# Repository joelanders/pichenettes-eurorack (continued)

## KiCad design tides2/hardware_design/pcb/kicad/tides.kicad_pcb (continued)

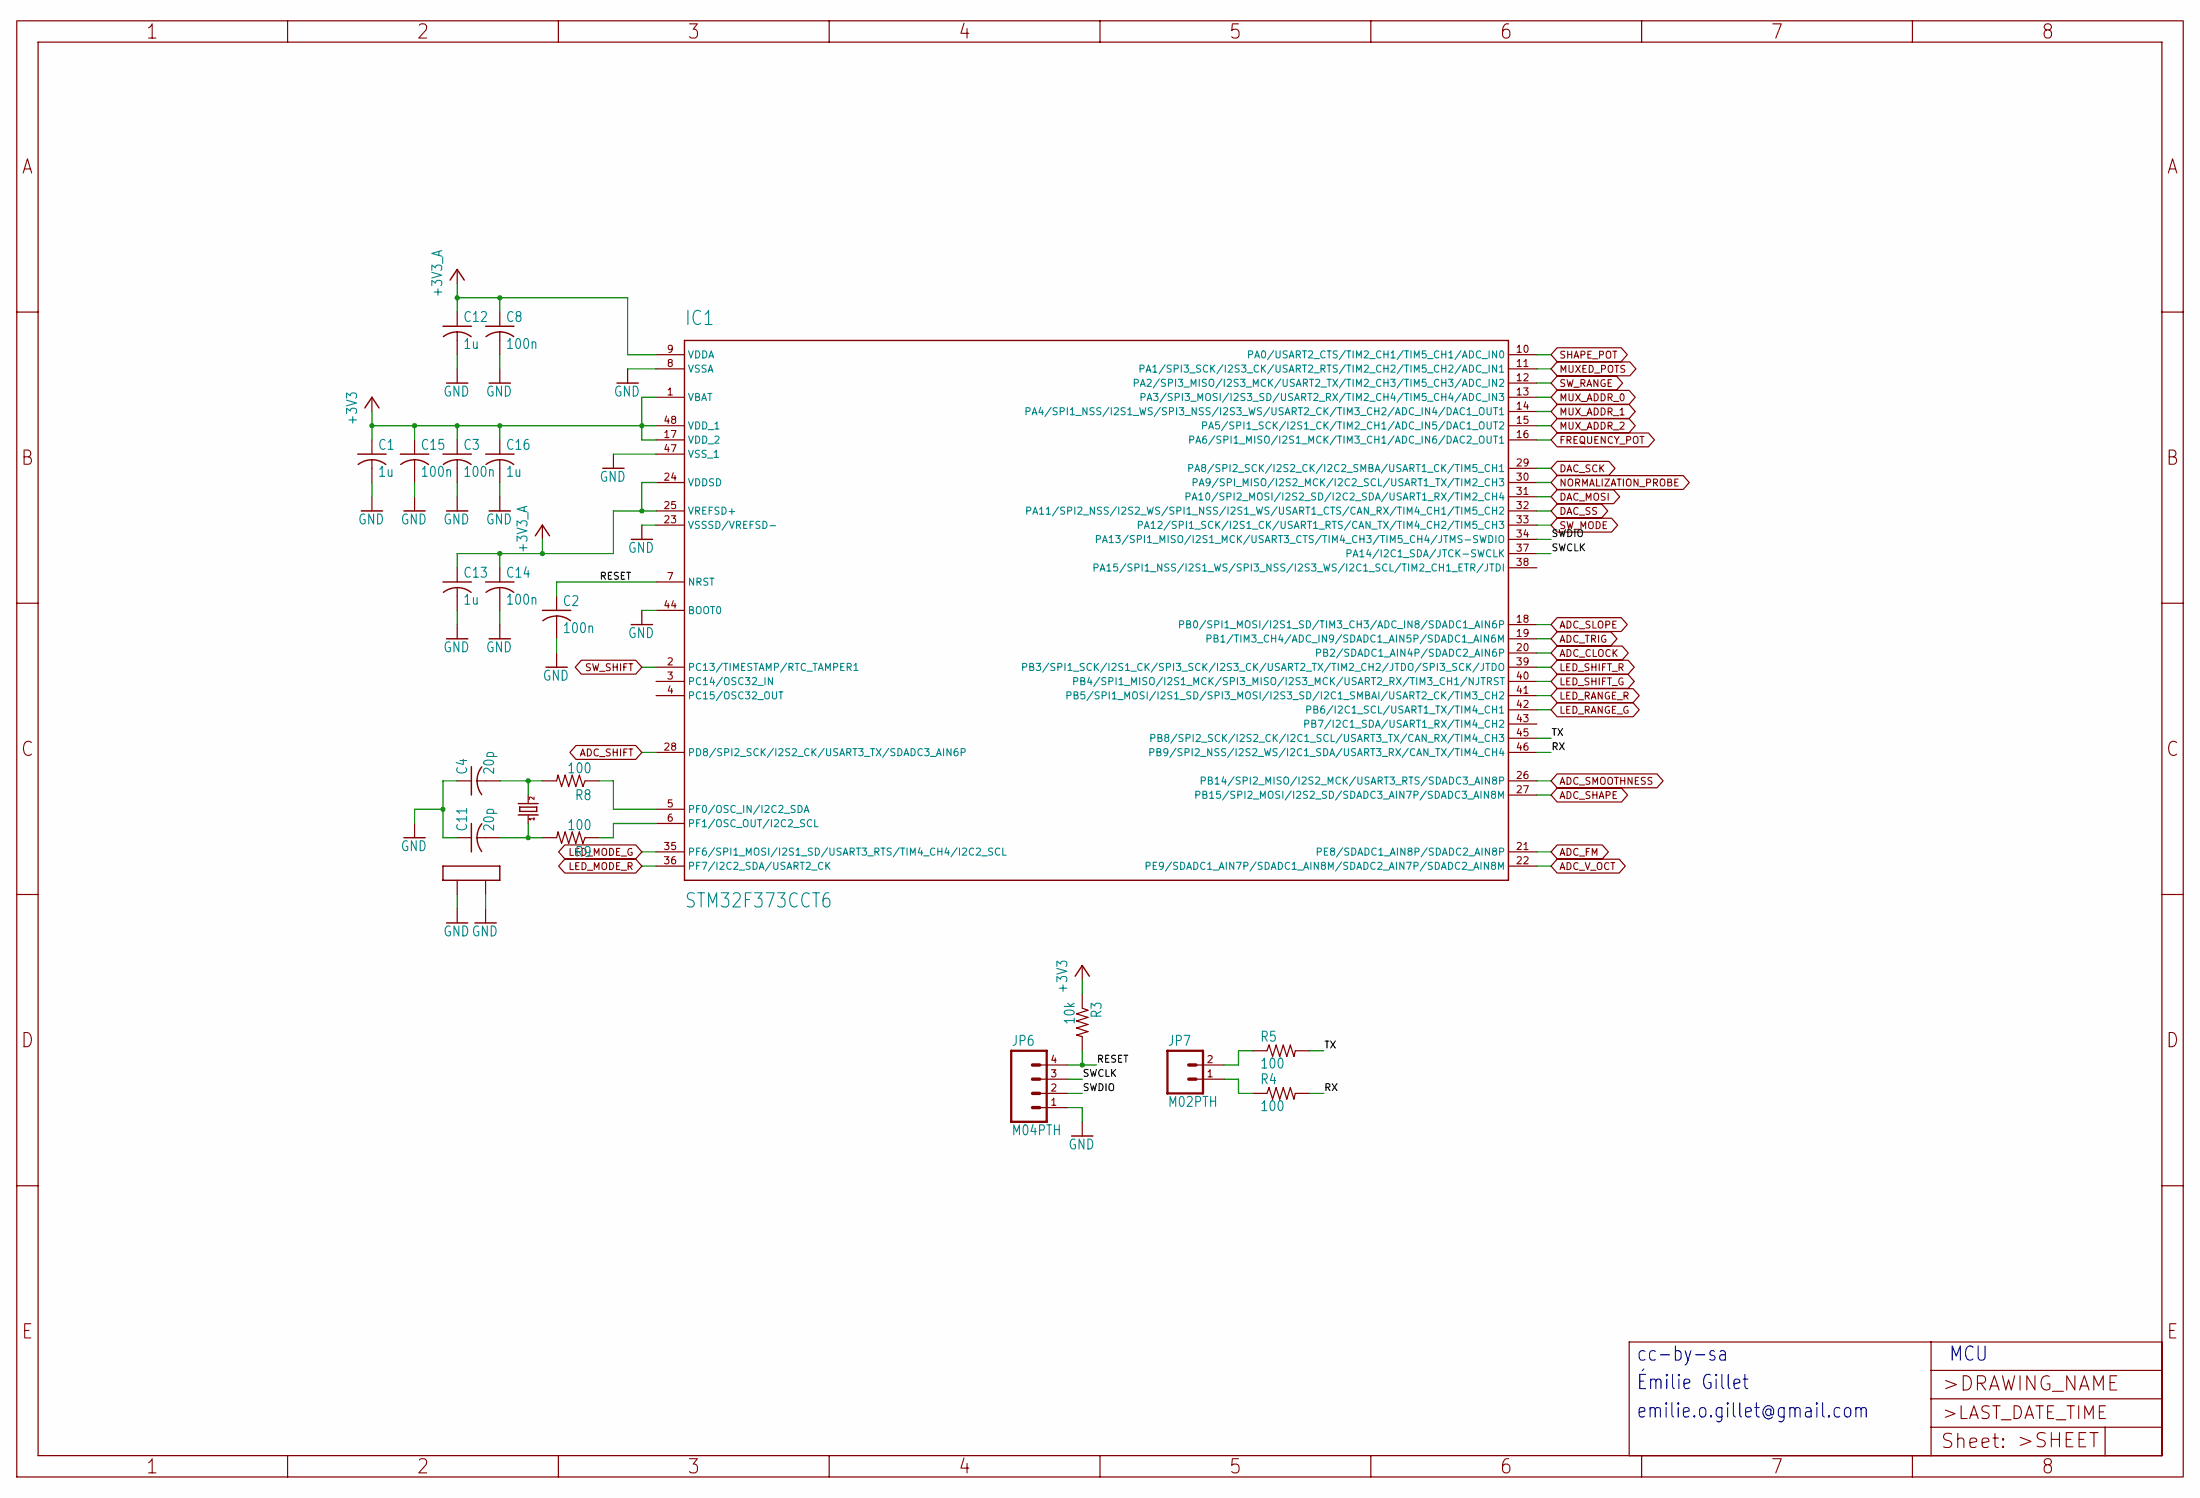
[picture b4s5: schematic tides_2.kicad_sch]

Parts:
C1, C12, C13, C16: 1u; C0402
C2, C3, C8, C14, C15: 100n; C0402
C4, C11: 20p; C0402
IC1: STM32F373CCT6; LQFP48
JP6: M04PTH; 1X04
JP7: M02PTH; 1X02
Q1: 8MHz; CTS406
R3: 10k; R0402
R4, R5, R8, R9: 100; R0402

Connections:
+3V3: C1.1, C3.1, C15.1, C16.1, IC1.1 (VBAT), IC1.17 (VDD_2), IC1.48 (VDD_1), R3.1; also elsewhere on the board
+3V3_A: C8.1, C12.1, C13.1, C14.1, IC1.9 (VDDA), IC1.24 (VDDSD), IC1.25 (VREFSD+); also elsewhere on the board
/tides_2/RESET: C2.1, IC1.7 (NRST), JP6.4, R3.2
/tides_2/RX: IC1.46 (PB9/SPI2_NSS/I2S2_WS/I2C1_SDA/USART3_RX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), R4.2
/tides_2/SWCLK: IC1.37 (PA14/I2C1_SDA/JTCK-SWCLK), JP6.3
/tides_2/SWDIO: IC1.34 (PA13/SPI1_MISO/I2S1_MCK/USART3_CTS/TIM4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), JP6.2
/tides_2/TX: IC1.45 (PB8/SPI2_SCK/I2S2_CK/I2C1_SCL/USART3_TX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), R5.2
ADC_CLOCK: IC1.20 (PB2/SDADC1_AIN4P/SDADC2_AIN6P); also elsewhere on the board
ADC_FM: IC1.21 (PE8/SDADC1_AIN8P/SDADC2_AIN8P); also elsewhere on the board
ADC_SHAPE: IC1.27 (PB15/SPI2_MOSI/I2S2_SD/SDADC3_AIN7P/SDA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); also elsewhere on the board
ADC_SHIFT: IC1.28 (PD8/SPI2_SCK/I2S2_CK/USART3_TX/SDADC3_A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); also elsewhere on the board
ADC_SLOPE: IC1.18 (PB0/SPI1_MOSI/I2S1_SD/TIM3_CH3/ADC_IN8/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); also elsewhere on the board
ADC_SMOOTHNESS: IC1.26 (PB14/SPI2_MISO/I2S2_MCK/USART3_RTS/SDAD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); also elsewhere on the board
ADC_TRIG: IC1.19 (PB1/TIM3_CH4/ADC_IN9/SDADC1_AIN5P/SDADC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); also elsewhere on the board
ADC_V_OCT: IC1.22 (PE9/SDADC1_AIN7P/SDADC1_AIN8M/SDADC2_AI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); also elsewhere on the board
DAC_MOSI: IC1.31 (PA10/SPI2_MOSI/I2S2_SD/I2C2_SDA/USART1_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); also elsewhere on the board
DAC_SCK: IC1.29 (PA8/SPI2_SCK/I2S2_CK/I2C2_SMBA/USART1_C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); also elsewhere on the board
DAC_SS: IC1.32 (PA11/SPI2_NSS/I2S2_WS/SPI1_NSS/I2S1_WS/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); also elsewhere on the board
FREQUENCY_POT: IC1.16 (PA6/SPI1_MISO/I2S1_MCK/TIM3_CH1/ADC_IN6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); also elsewhere on the board
GND: C1.2, C2.2, C3.2, C4.1, C8.2, C11.1, C12.2, C13.2, C14.2, C15.2, C16.2, IC1.8 (VSSA), IC1.23 (VSSSD/VREFSD-), IC1.44 (BOOT0), IC1.47 (VSS_1), JP6.1, Q1.2 (LID1), Q1.4 (LID2); also elsewhere on the board
LED_MODE_G: IC1.35 (PF6/SPI1_MOSI/I2S1_SD/USART3_RTS/TIM4_C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); also elsewhere on the board
LED_MODE_R: IC1.36 (PF7/I2C2_SDA/USART2_CK); also elsewhere on the board
LED_RANGE_G: IC1.42 (PB6/I2C1_SCL/USART1_TX/TIM4_CH1); also elsewhere on the board
LED_RANGE_R: IC1.41 (PB5/SPI1_MOSI/I2S1_SD/SPI3_MOSI/I2S3_SD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); also elsewhere on the board
LED_SHIFT_G: IC1.40 (PB4/SPI1_MISO/I2S1_MCK/SPI3_MISO/I2S3_M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); also elsewhere on the board
LED_SHIFT_R: IC1.39 (PB3/SPI1_SCK/I2S1_CK/SPI3_SCK/I2S3_CK/U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); also elsewhere on the board
MUXED_POTS: IC1.11 (PA1/SPI3_SCK/I2S3_CK/USART2_RTS/TIM2_CH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); also elsewhere on the board
MUX_ADDR_0: IC1.13 (PA3/SPI3_MOSI/I2S3_SD/USART2_RX/TIM2_CH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); also elsewhere on the board
MUX_ADDR_1: IC1.14 (PA4/SPI1_NSS/I2S1_WS/SPI3_NSS/I2S3_WS/U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); also elsewhere on the board
MUX_ADDR_2: IC1.15 (PA5/SPI1_SCK/I2S1_CK/TIM2_CH1/ADC_IN5/D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); also elsewhere on the board
NORMALIZATION_PROBE: IC1.30 (PA9/SPI_MISO/I2S2_MCK/I2C2_SCL/USART1_T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); also elsewhere on the board
unnamed: C4.2, Q1.3 (2), R8.2
unnamed: C11.2, Q1.1, R9.2
unnamed: IC1.5 (PF0/OSC_IN/I2C2_SDA), R8.1
unnamed: IC1.6 (PF1/OSC_OUT/I2C2_SCL), R9.1
unnamed: JP7.1, R4.1
unnamed: JP7.2, R5.1
SHAPE_POT: IC1.10 (PA0/USART2_CTS/TIM2_CH1/TIM5_CH1/ADC_IN0); also elsewhere on the board
SW_MODE: IC1.33 (PA12/SPI1_SCK/I2S1_CK/USART1_RTS/CAN_TX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); also elsewhere on the board
SW_RANGE: IC1.12 (PA2/SPI3_MISO/I2S3_MCK/USART2_TX/TIM2_C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); also elsewhere on the board
SW_SHIFT: IC1.2 (PC13/TIMESTAMP/RTC_TAMPER1); also elsewhere on the board

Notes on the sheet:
emilie.o.gillet@gmail.com
cc-by-sa
Émilie Gillet
MCU

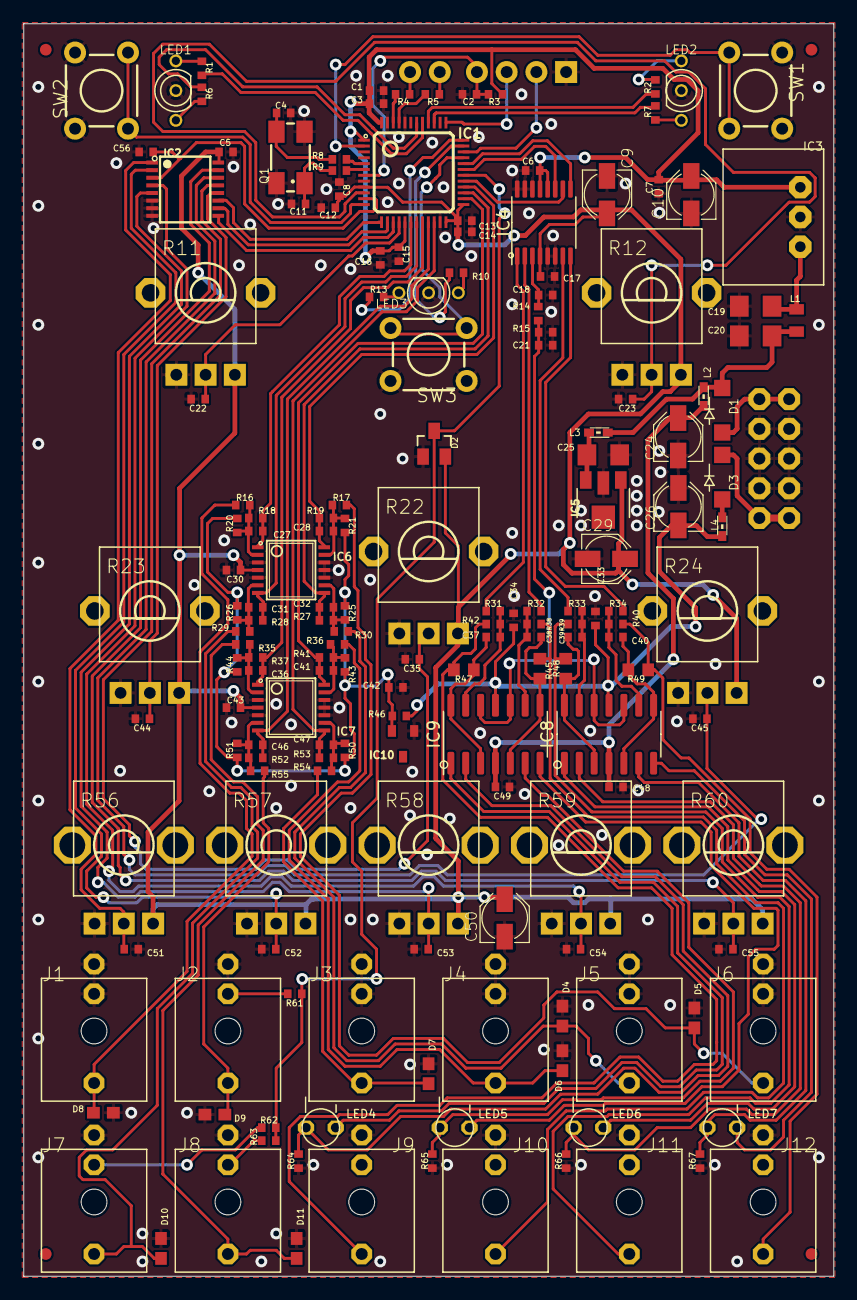
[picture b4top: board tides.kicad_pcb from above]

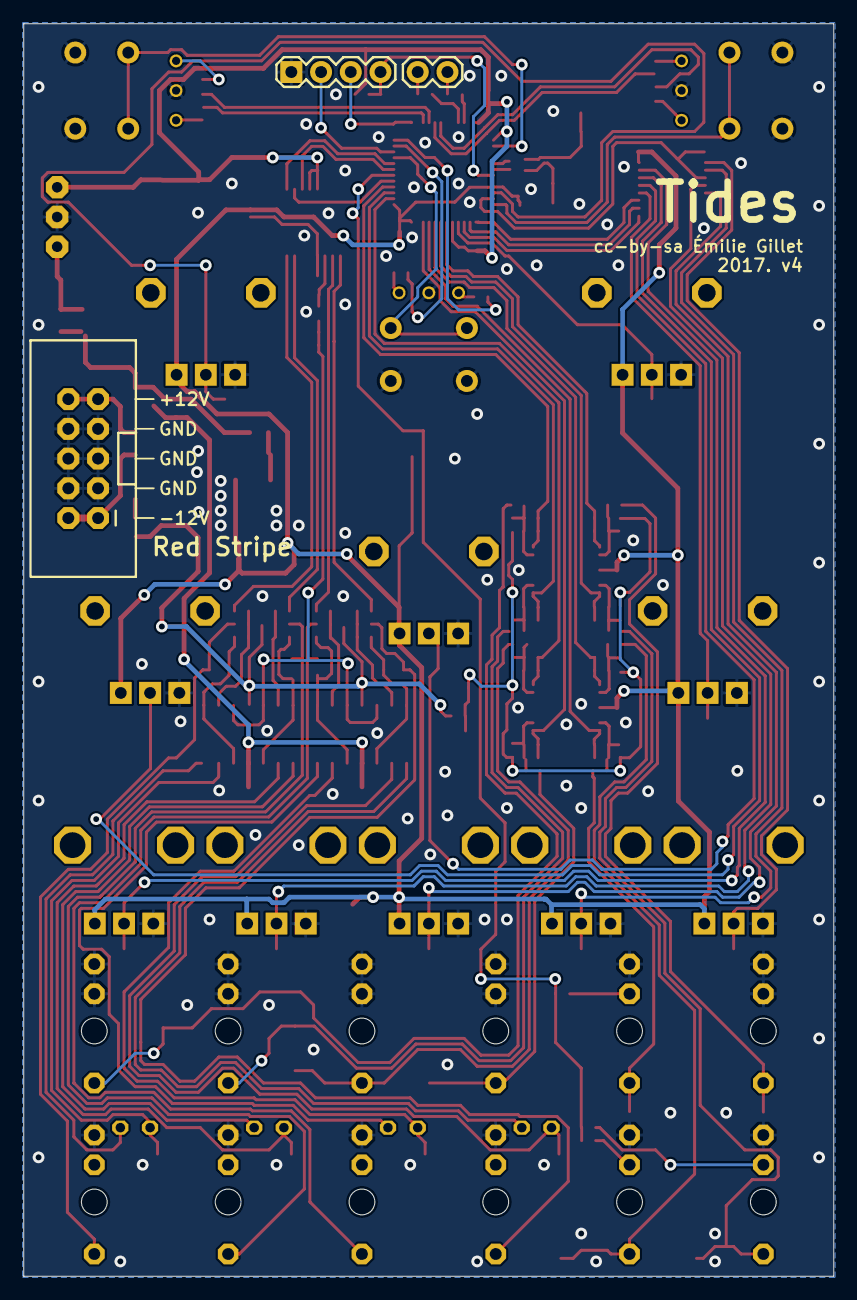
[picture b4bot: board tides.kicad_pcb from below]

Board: 2 copper layers, 69.2 x 107.0 mm, 178 parts (3 on the bottom side), 109 nets.

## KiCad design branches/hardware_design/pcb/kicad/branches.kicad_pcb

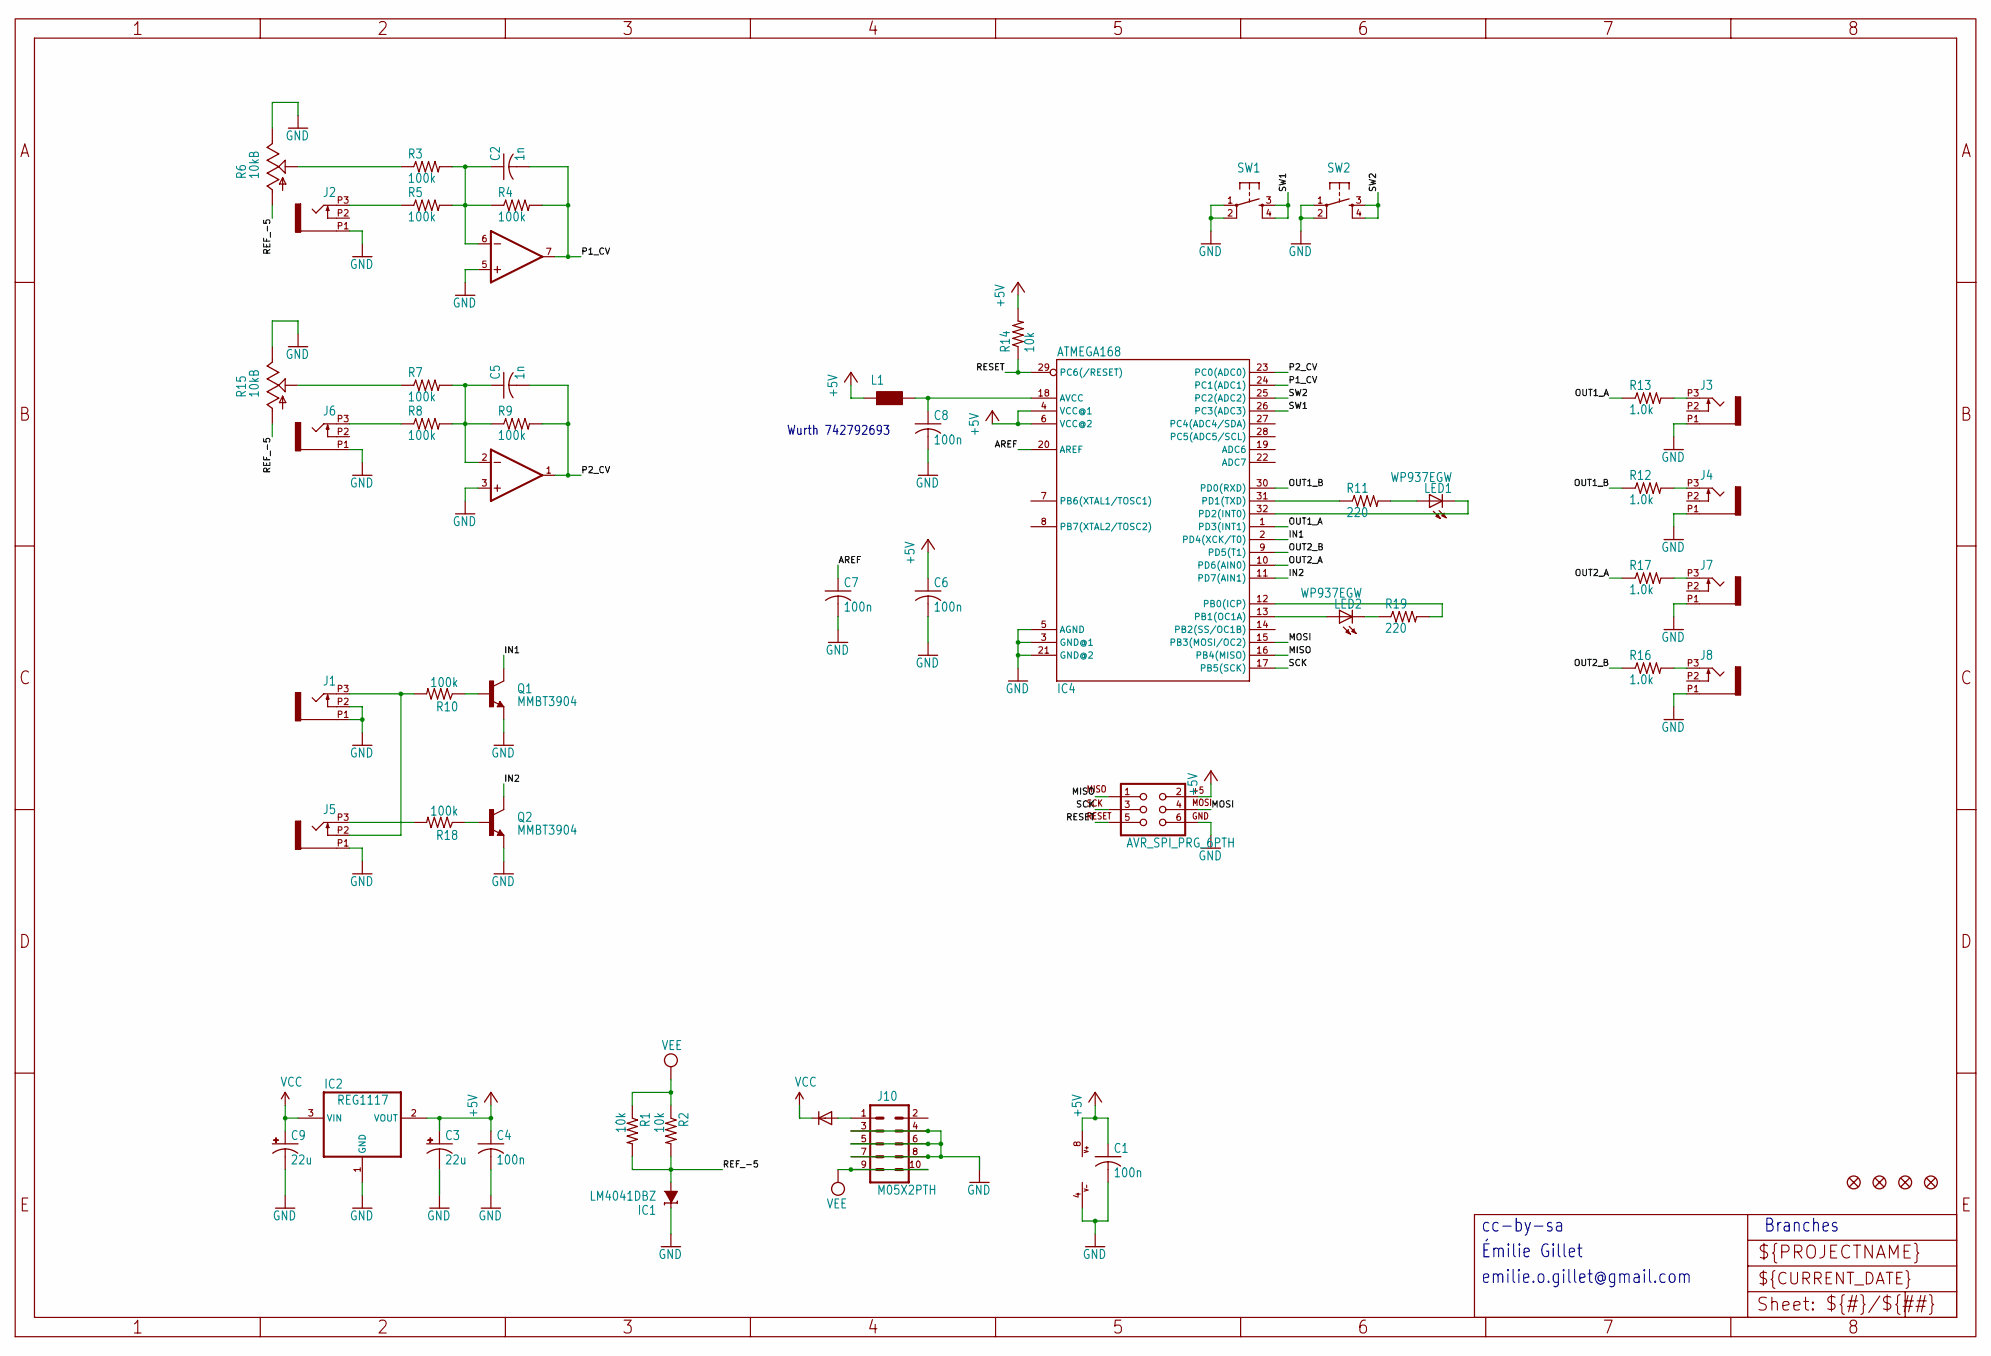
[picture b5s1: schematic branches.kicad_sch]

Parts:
C1, C4, C6, C7, C8: 100n; C0603
C2, C5: 1n; C0603
C3, C9: 22u; PANASONIC_C
D1: 1N5819HW; SOD123
F1, F2, F3, F4: FIDUCIAL1X2; FIDUCIAL-1X2
IC1: LM4041DBZ; DBZ_R-PDSO-G3
IC2: REG1117; SOT223
IC3: TL072D; SO08
IC4: ATMEGA168; TQFP32-08
J1, J2, J3, J4, J5, J6, J7, J8: PJ301_THONKICONN6; WQP_PJ_301M6
J9: AVR_SPI_PRG_6PTH; 2X3
J10: M05X2PTH; AVR_ICSP
L1: WE-CBF_0603; 0603
LED1, LED2: WP937EGW; LED3MM
Q1, Q2: MMBT3904; SOT23-BEC
R1, R2, R14: 10k; R0603
R3, R4, R5, R7, R8, R9, R10, R18: 100k; R0603
R6, R15: 10kB; ALPS_POT_VERTICAL_PS
R11, R19: 220; R0603
R12, R13, R16, R17: 1.0k; R0603
SW1, SW2: TAC_SWITCHPTH; TACTILE-PTH

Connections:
+5V: C1.1, C3.+, C4.1, C6.1, IC2.2 (VOUT), IC3.8 (V+), IC4.4 (VCC@1), IC4.6 (VCC@2), J9.2, L1.1, R14.2
AREF: C7.1, IC4.20 (AREF)
GATE1_IN: J1.P3 (3), J5.P2 (2), R10.2
GATE2_IN: J5.P3 (3), R18.2
GND: C1.2, C3.-, C4.2, C6.2, C7.2, C8.2, C9.-, IC1.1 (C), IC2.1 (GND), IC3.3 (+IN), IC3.4 (V-), IC3.5 (+IN), IC4.3 (GND@1), IC4.5 (AGND), IC4.21 (GND@2), J1.P1 (1), J1.P2 (2), J2.P1 (1), J3.P1 (1), J4.P1 (1), J5.P1 (1), J6.P1 (1), J7.P1 (1), J8.P1 (1), J9.6, J10.3, J10.4, J10.5, J10.6, J10.7, J10.8, Q1.E, Q2.E, R6.P$1 (E), R15.P$1 (E), SW1.1, SW1.2, SW2.1, SW2.2
IN1: IC4.2 (PD4(XCK/T0)), Q1.C
IN2: IC4.11 (PD7(AIN1)), Q2.C
MISO: IC4.16 (PB4(MISO)), J9.1
MOSI: IC4.15 (PB3(MOSI/OC2)), J9.4
unnamed: Q1.B, R10.1
unnamed: Q2.B, R18.1
unnamed: D1.A, J10.1
unnamed: C5.1, IC3.2 (-IN), R7.2, R8.2, R9.1
unnamed: J8.P3 (3), R16.2
unnamed: R7.1, R15.P$2 (S)
unnamed: R3.1, R6.P$2 (S)
unnamed: J2.P3 (3), R5.1
unnamed: J6.P3 (3), R8.1
unnamed: IC4.31 (PD1(TXD)), R11.1
unnamed: LED1.A, R11.2
unnamed: IC4.32 (PD2(INT0)), LED1.K (C)
unnamed: IC4.13 (PB1(OC1A)), LED2.A
unnamed: LED2.K (C), R19.1
unnamed: IC4.12 (PB0(ICP)), R19.2
unnamed: C2.1, IC3.6 (-IN), R3.2, R4.1, R5.2
unnamed: J3.P3 (3), R13.2
unnamed: J4.P3 (3), R12.2
unnamed: J7.P3 (3), R17.2
unnamed: C8.1, IC4.18 (AVCC), L1.2
OUT1_A: IC4.1 (PD3(INT1)), R13.1
OUT1_B: IC4.30 (PD0(RXD)), R12.1
OUT2_A: IC4.10 (PD6(AIN0)), R17.1
OUT2_B: IC4.9 (PD5(T1)), R16.1
P1_CV: C2.2, IC3.7 (OUT), IC4.24 (PC1(ADC1)), R4.2
P2_CV: C5.2, IC3.1 (OUT), IC4.23 (PC0(ADC0)), R9.2
REF_-5: IC1.2 (A), R1.2, R2.2, R6.P$3 (A), R15.P$3 (A)
RESET: IC4.29 (PC6(/RESET)), J9.5, R14.1
SCK: IC4.17 (PB5(SCK)), J9.3
SW1: IC4.26 (PC3(ADC3)), SW1.3, SW1.4
SW2: IC4.25 (PC2(ADC2)), SW2.3, SW2.4
VCC: C9.+, D1.C, IC2.3 (VIN)
VEE: J10.9, J10.10, R1.1, R2.1

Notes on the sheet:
Émilie Gillet
emilie.o.gillet@gmail.com
Branches
Wurth 742792693
cc-by-sa

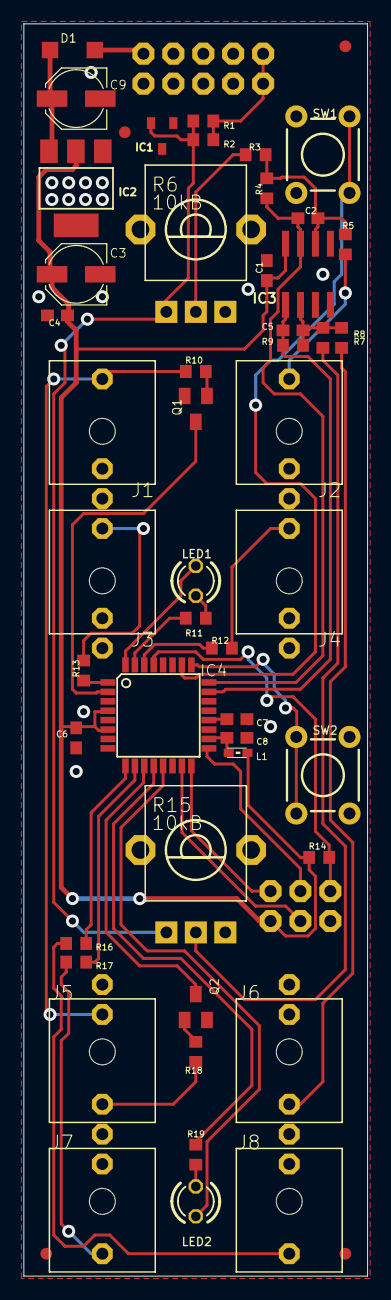
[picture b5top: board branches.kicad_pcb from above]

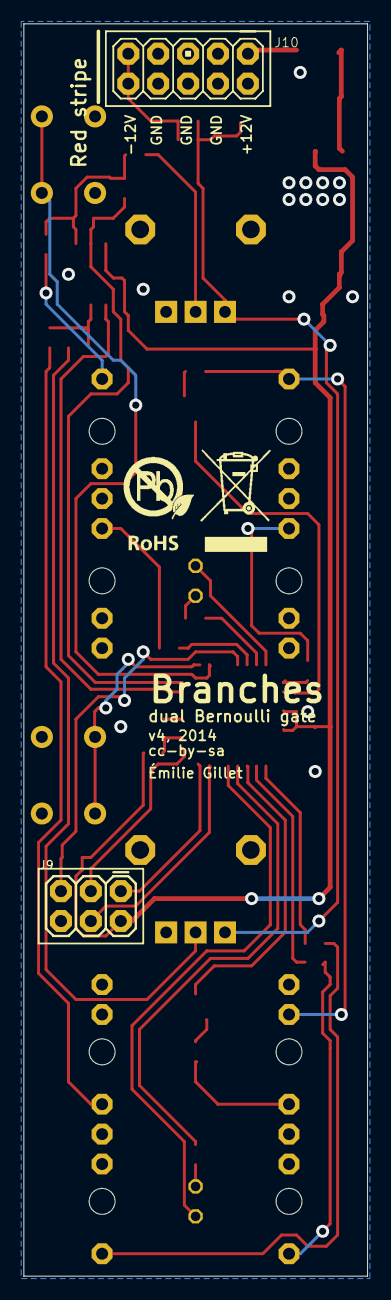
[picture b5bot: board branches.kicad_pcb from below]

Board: 2 copper layers, 29.2 x 106.4 mm, 55 parts (3 on the bottom side), 42 nets.

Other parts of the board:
U$1: ROHS

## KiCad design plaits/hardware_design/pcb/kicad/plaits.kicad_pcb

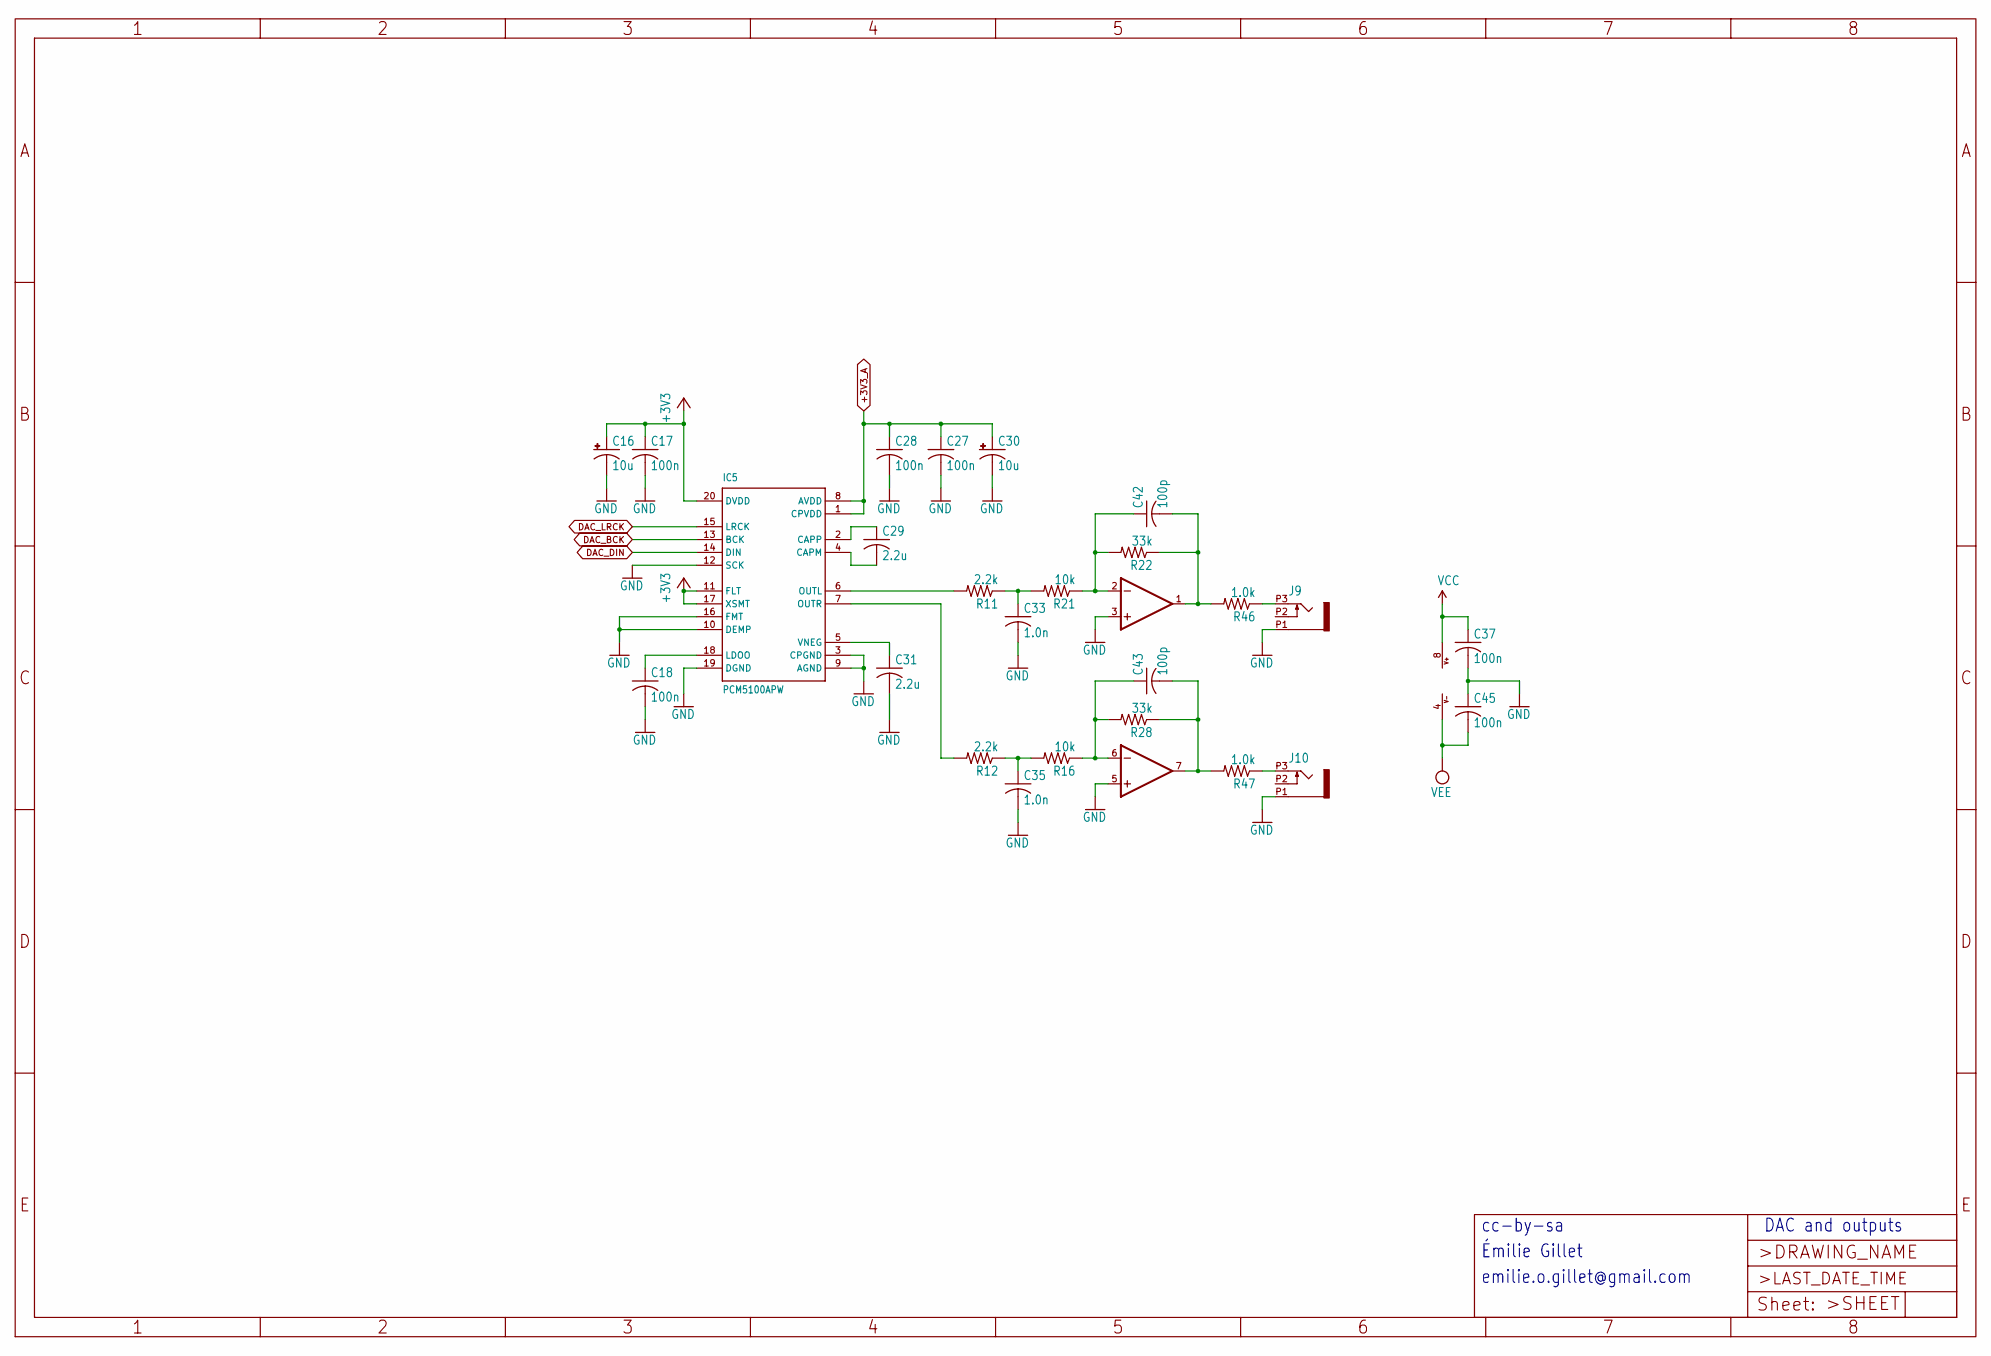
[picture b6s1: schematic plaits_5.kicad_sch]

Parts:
C16, C30: 10u; PANASONIC_B
C17, C18, C27, C28, C37, C45: 100n; C0402
C29, C31: 2.2u; C0805
C33, C35: 1.0n; C0402
C42, C43: 100p; C0402
IC5: PCM5100APW; SSOP20
IC8: TL072PW; TSSOP08
J9, J10: PJ301_THONKICONN6; WQP_PJ_301M6
R11, R12: 2.2k; R0402
R16, R21: 10k; R0402
R22, R28: 33k; R0402
R46, R47: 1.0k; R0603

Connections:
+3V3: C16.+, C17.1, IC5.11 (FLT), IC5.17 (XSMT), IC5.20 (DVDD); also elsewhere on the board
+3V3_A: C27.1, C28.1, C30.+, IC5.1 (CPVDD), IC5.8 (AVDD); also elsewhere on the board
DAC_BCK: IC5.13 (BCK); also elsewhere on the board
DAC_DIN: IC5.14 (DIN); also elsewhere on the board
DAC_LRCK: IC5.15 (LRCK); also elsewhere on the board
GND: C16.-, C17.2, C18.2, C27.2, C28.2, C30.-, C31.2, C33.2, C35.2, C37.2, C45.1, IC5.3 (CPGND), IC5.9 (AGND), IC5.10 (DEMP), IC5.12 (SCK), IC5.16 (FMT), IC5.19 (DGND), IC8.3 (+IN), IC8.5 (+IN), J9.P1 (1), J10.P1 (1); also elsewhere on the board
unnamed: C33.1, R11.1, R21.2
unnamed: C35.1, R12.1, R16.2
unnamed: C29.2, IC5.4 (CAPM)
unnamed: C29.1, IC5.2 (CAPP)
unnamed: C18.1, IC5.18 (LDOO)
unnamed: IC5.6 (OUTL), R11.2
unnamed: IC5.7 (OUTR), R12.2
unnamed: C31.1, IC5.5 (VNEG)
unnamed: C42.1, IC8.2 (-IN), R21.1, R22.2
unnamed: C42.2, IC8.1 (OUT), R22.1, R46.2
unnamed: C43.1, IC8.6 (-IN), R16.1, R28.2
unnamed: C43.2, IC8.7 (OUT), R28.1, R47.2
unnamed: J9.P3 (3), R46.1
unnamed: J10.P3 (3), R47.1
VCC: C37.1, IC8.8 (V+); also elsewhere on the board
VEE: C45.2, IC8.4 (V-); also elsewhere on the board

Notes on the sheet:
Émilie Gillet
DAC and outputs
cc-by-sa
emilie.o.gillet@gmail.com

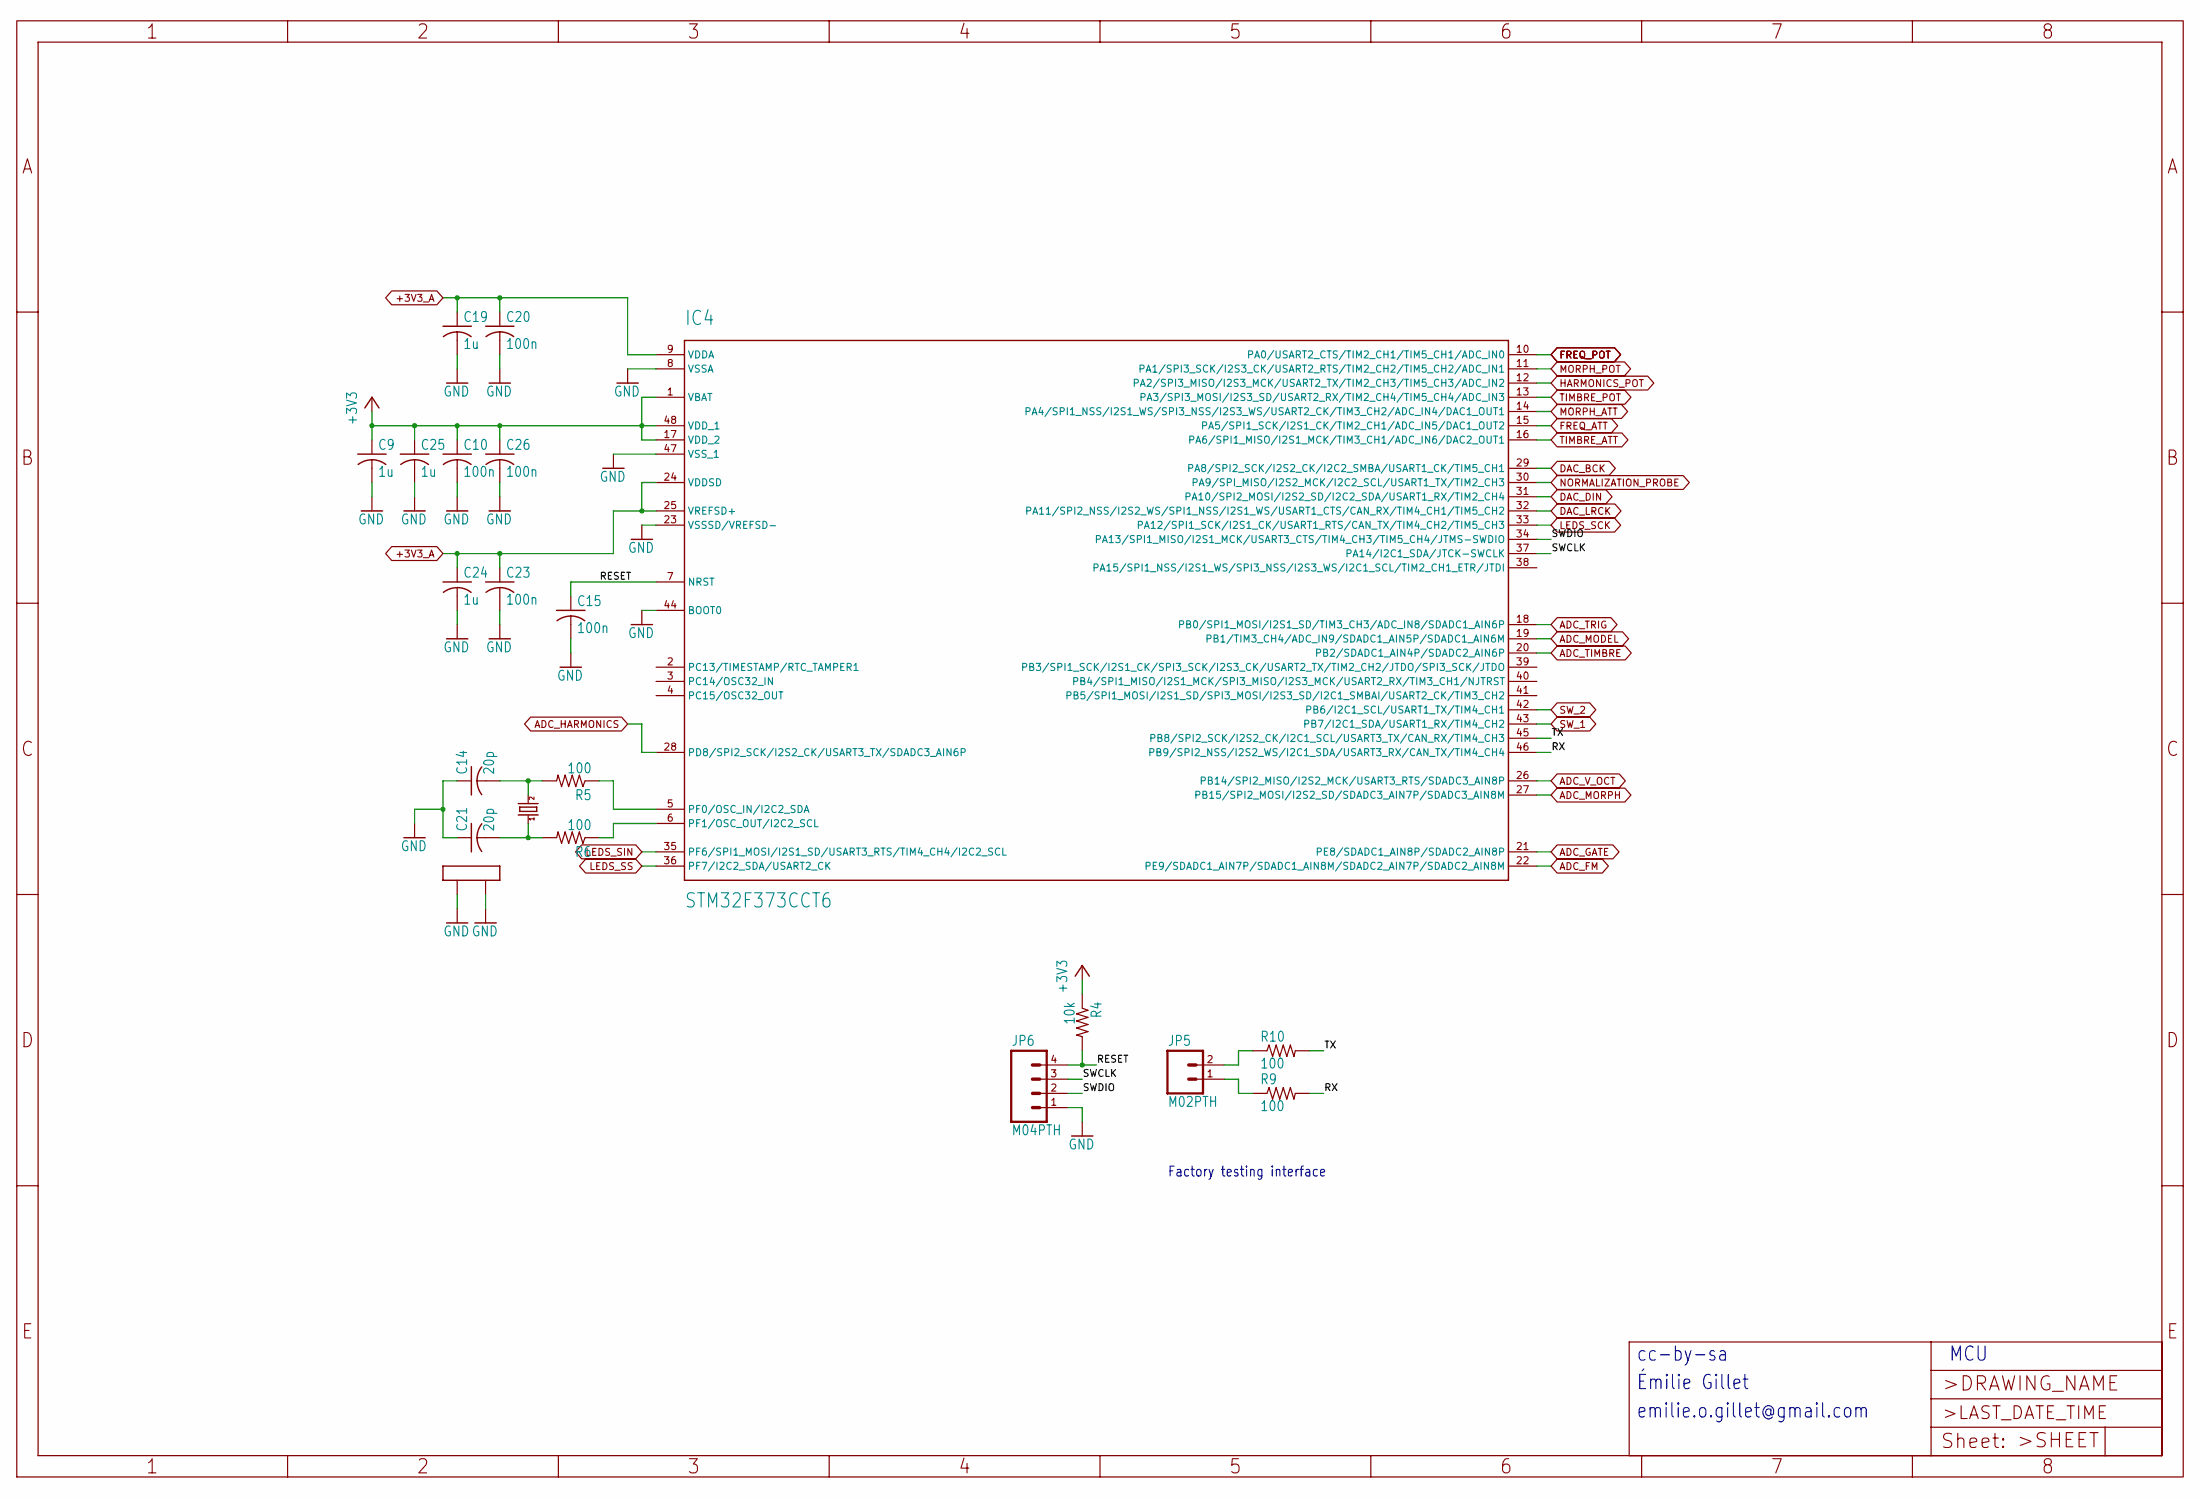
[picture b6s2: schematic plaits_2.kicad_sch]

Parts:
C9, C19, C24, C25: 1u; C0402
C10, C15, C20, C23, C26: 100n; C0402
C14, C21: 20p; C0402
IC4: STM32F373CCT6; LQFP48
JP5: M02PTH; 1X02
JP6: M04PTH; 1X04
Q1: 8MHz; CTS406
R4: 10k; R0402
R5, R6, R9, R10: 100; R0402

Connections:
+3V3: C9.1, C10.1, C25.1, C26.1, IC4.1 (VBAT), IC4.17 (VDD_2), IC4.48 (VDD_1), R4.1; also elsewhere on the board
+3V3_A: C19.1, C20.1, C23.1, C24.1, IC4.9 (VDDA), IC4.24 (VDDSD), IC4.25 (VREFSD+); also elsewhere on the board
/plaits_2/RESET: C15.1, IC4.7 (NRST), JP6.4, R4.2
/plaits_2/RX: IC4.46 (PB9/SPI2_NSS/I2S2_WS/I2C1_SDA/USART3_RX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), R9.2
/plaits_2/SWCLK: IC4.37 (PA14/I2C1_SDA/JTCK-SWCLK), JP6.3
/plaits_2/SWDIO: IC4.34 (PA13/SPI1_MISO/I2S1_MCK/USART3_CTS/TIM4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), JP6.2
/plaits_2/TX: IC4.45 (PB8/SPI2_SCK/I2S2_CK/I2C1_SCL/USART3_TX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), R10.2
ADC_FM: IC4.22 (PE9/SDADC1_AIN7P/SDADC1_AIN8M/SDADC2_AI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); also elsewhere on the board
ADC_GATE: IC4.21 (PE8/SDADC1_AIN8P/SDADC2_AIN8P); also elsewhere on the board
ADC_HARMONICS: IC4.28 (PD8/SPI2_SCK/I2S2_CK/USART3_TX/SDADC3_A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); also elsewhere on the board
ADC_MODEL: IC4.19 (PB1/TIM3_CH4/ADC_IN9/SDADC1_AIN5P/SDADC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); also elsewhere on the board
ADC_MORPH: IC4.27 (PB15/SPI2_MOSI/I2S2_SD/SDADC3_AIN7P/SDA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); also elsewhere on the board
ADC_TIMBRE: IC4.20 (PB2/SDADC1_AIN4P/SDADC2_AIN6P); also elsewhere on the board
ADC_TRIG: IC4.18 (PB0/SPI1_MOSI/I2S1_SD/TIM3_CH3/ADC_IN8/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); also elsewhere on the board
ADC_V_OCT: IC4.26 (PB14/SPI2_MISO/I2S2_MCK/USART3_RTS/SDAD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); also elsewhere on the board
DAC_BCK: IC4.29 (PA8/SPI2_SCK/I2S2_CK/I2C2_SMBA/USART1_C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); also elsewhere on the board
DAC_DIN: IC4.31 (PA10/SPI2_MOSI/I2S2_SD/I2C2_SDA/USART1_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); also elsewhere on the board
DAC_LRCK: IC4.32 (PA11/SPI2_NSS/I2S2_WS/SPI1_NSS/I2S1_WS/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); also elsewhere on the board
FREQ_ATT: IC4.15 (PA5/SPI1_SCK/I2S1_CK/TIM2_CH1/ADC_IN5/D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); also elsewhere on the board
FREQ_POT: IC4.10 (PA0/USART2_CTS/TIM2_CH1/TIM5_CH1/ADC_IN0); also elsewhere on the board
GND: C9.2, C10.2, C14.1, C15.2, C19.2, C20.2, C21.1, C23.2, C24.2, C25.2, C26.2, IC4.8 (VSSA), IC4.23 (VSSSD/VREFSD-), IC4.44 (BOOT0), IC4.47 (VSS_1), JP6.1, Q1.2 (LID1), Q1.4 (LID2); also elsewhere on the board
HARMONICS_POT: IC4.12 (PA2/SPI3_MISO/I2S3_MCK/USART2_TX/TIM2_C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); also elsewhere on the board
LEDS_SCK: IC4.33 (PA12/SPI1_SCK/I2S1_CK/USART1_RTS/CAN_TX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); also elsewhere on the board
LEDS_SIN: IC4.35 (PF6/SPI1_MOSI/I2S1_SD/USART3_RTS/TIM4_C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); also elsewhere on the board
LEDS_SS: IC4.36 (PF7/I2C2_SDA/USART2_CK); also elsewhere on the board
MORPH_ATT: IC4.14 (PA4/SPI1_NSS/I2S1_WS/SPI3_NSS/I2S3_WS/U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); also elsewhere on the board
MORPH_POT: IC4.11 (PA1/SPI3_SCK/I2S3_CK/USART2_RTS/TIM2_CH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); also elsewhere on the board
NORMALIZATION_PROBE: IC4.30 (PA9/SPI_MISO/I2S2_MCK/I2C2_SCL/USART1_T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); also elsewhere on the board
unnamed: C21.2, Q1.1, R6.2
unnamed: IC4.5 (PF0/OSC_IN/I2C2_SDA), R5.1
unnamed: IC4.6 (PF1/OSC_OUT/I2C2_SCL), R6.1
unnamed: JP5.1, R9.1
unnamed: JP5.2, R10.1
unnamed: C14.2, Q1.3 (2), R5.2
SW_1: IC4.43 (PB7/I2C1_SDA/USART1_RX/TIM4_CH2); also elsewhere on the board
SW_2: IC4.42 (PB6/I2C1_SCL/USART1_TX/TIM4_CH1); also elsewhere on the board
TIMBRE_ATT: IC4.16 (PA6/SPI1_MISO/I2S1_MCK/TIM3_CH1/ADC_IN6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); also elsewhere on the board
TIMBRE_POT: IC4.13 (PA3/SPI3_MOSI/I2S3_SD/USART2_RX/TIM2_CH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); also elsewhere on the board

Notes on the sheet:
Factory testing interface
cc-by-sa
emilie.o.gillet@gmail.com
MCU
Émilie Gillet
